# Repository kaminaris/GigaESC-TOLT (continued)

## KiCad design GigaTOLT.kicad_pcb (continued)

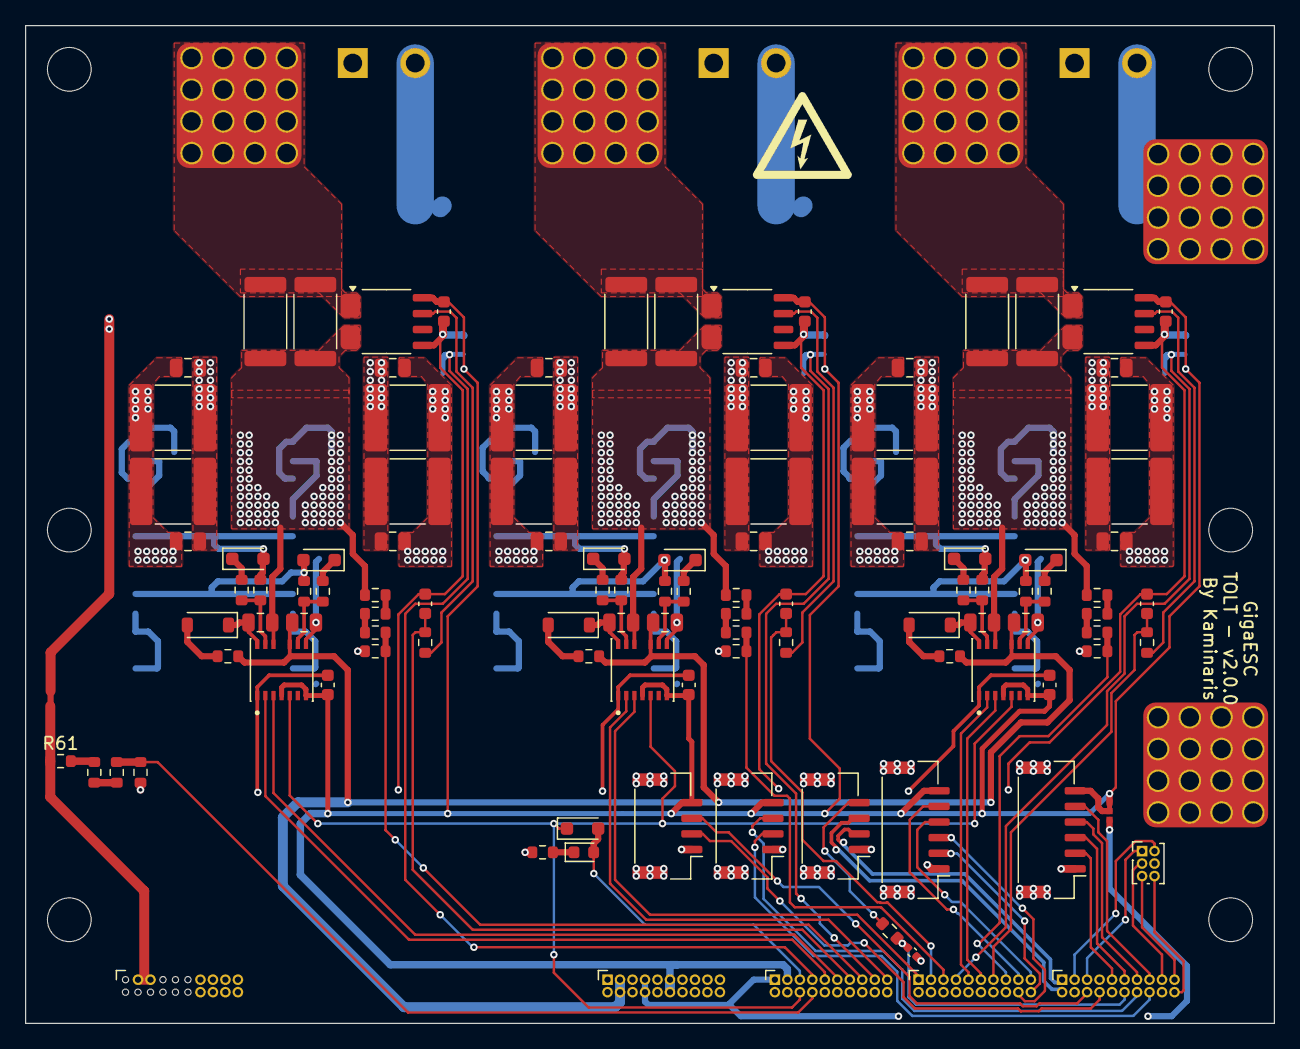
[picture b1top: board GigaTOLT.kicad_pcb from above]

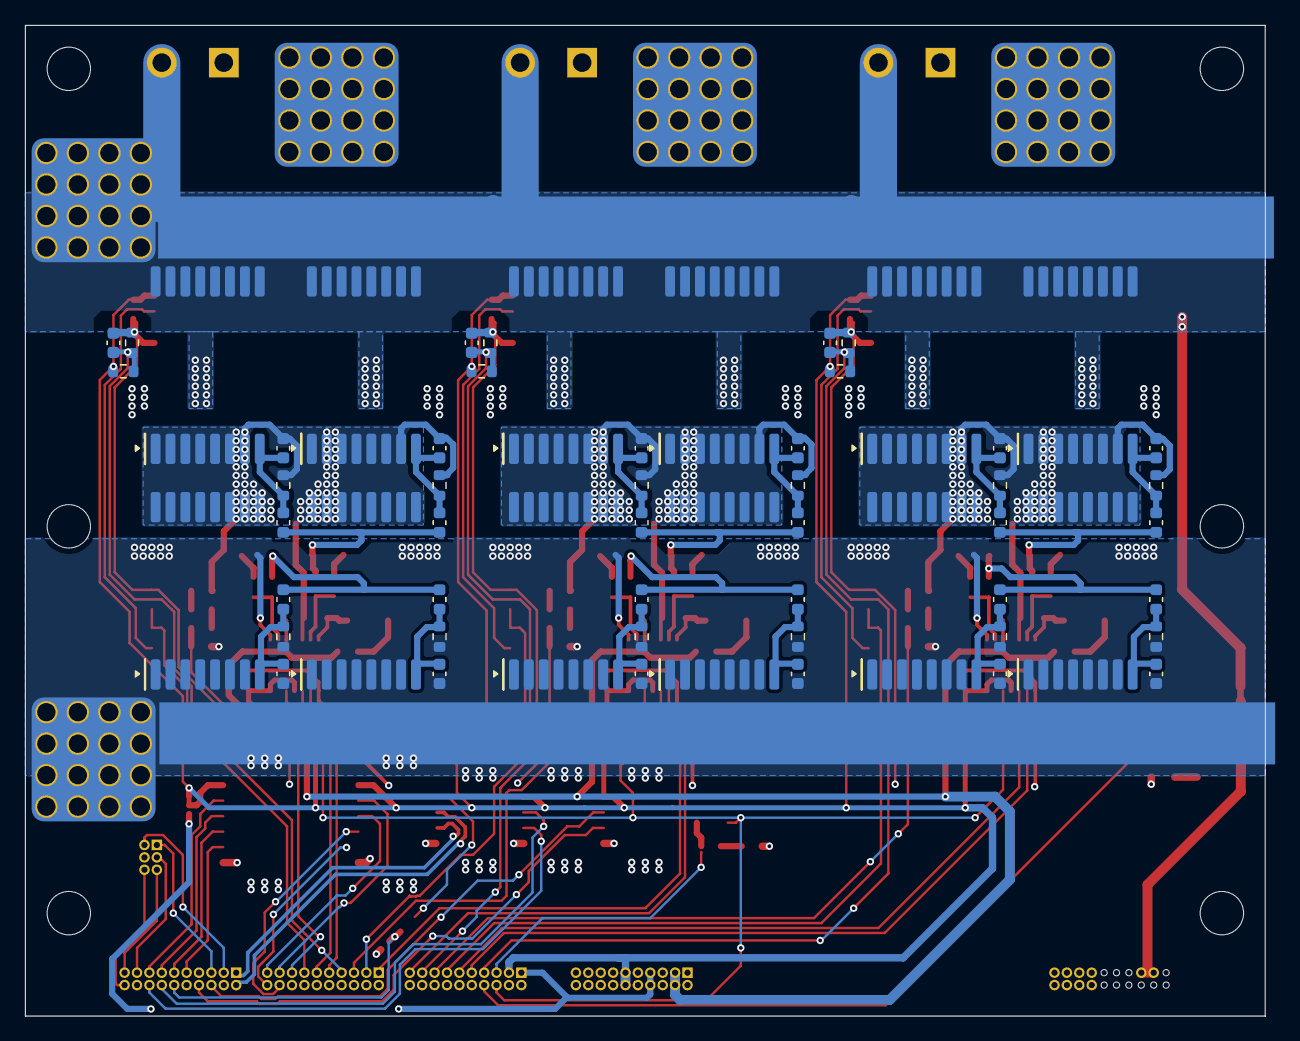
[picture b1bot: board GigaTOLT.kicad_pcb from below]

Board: 4 copper layers, 100.0 x 79.9 mm, 182 parts (59 on the bottom side), 100 nets.
